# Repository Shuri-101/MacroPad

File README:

#Fracture Pad (A macro pad project) 
A macro Pad for use in CAD and general productivity + convenience, mainly for use in CAD... but up to you to decide what you want to use it for, I included an OLED screen to display things like animations or info like RAM usage...
# Orpheuspad

Orpheuspad is a 4 key macropad with a rotary encoder, an OLED Display. It also has 2 WS2812B Leds, and uses QMK firmware

It serves as an example piece/reference for the hackpad YSWS, since it contains an implementation of every common part.

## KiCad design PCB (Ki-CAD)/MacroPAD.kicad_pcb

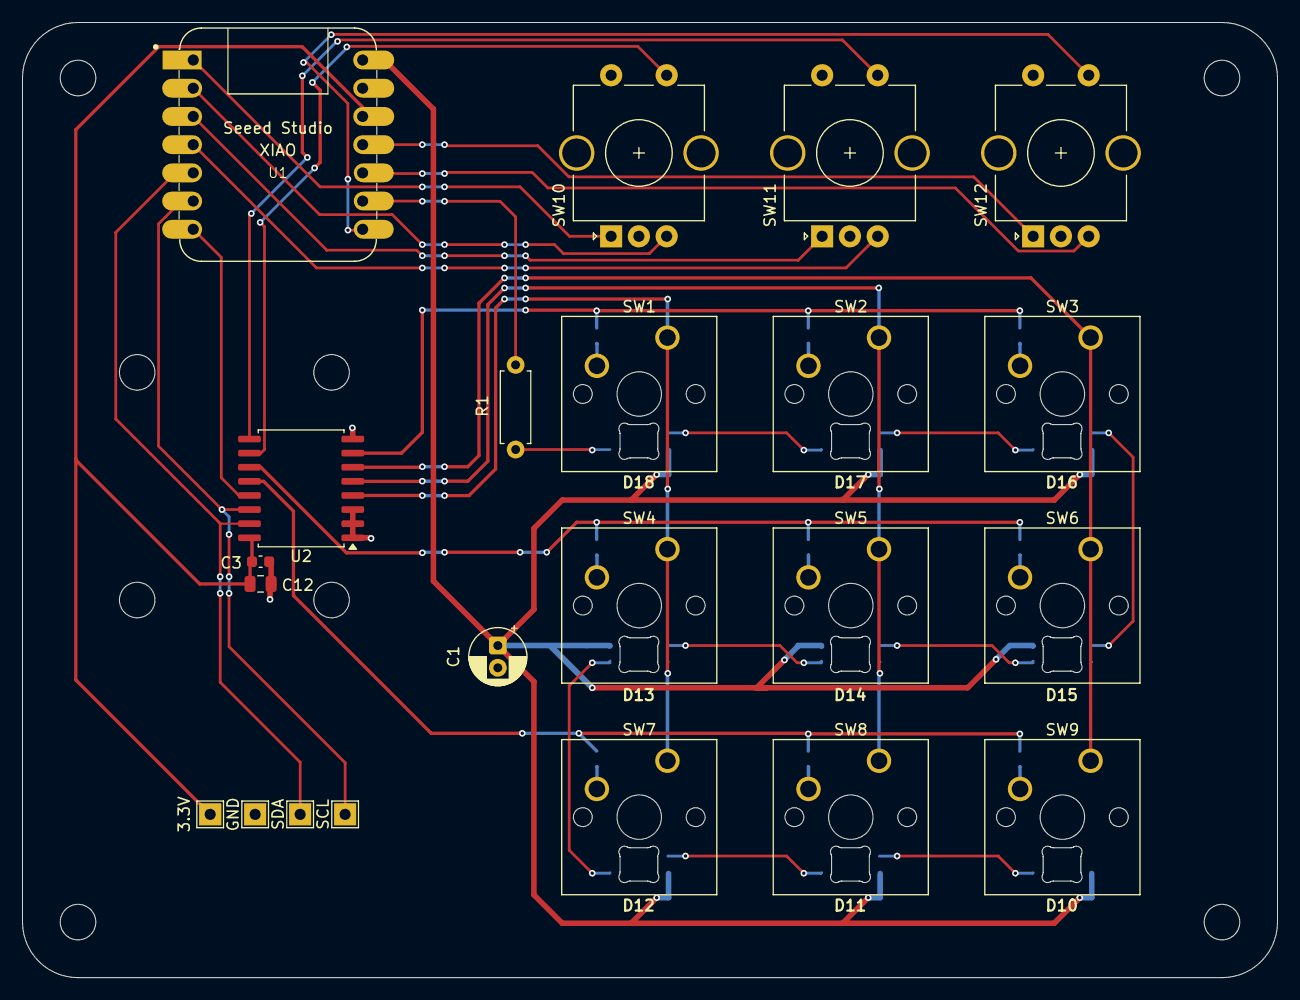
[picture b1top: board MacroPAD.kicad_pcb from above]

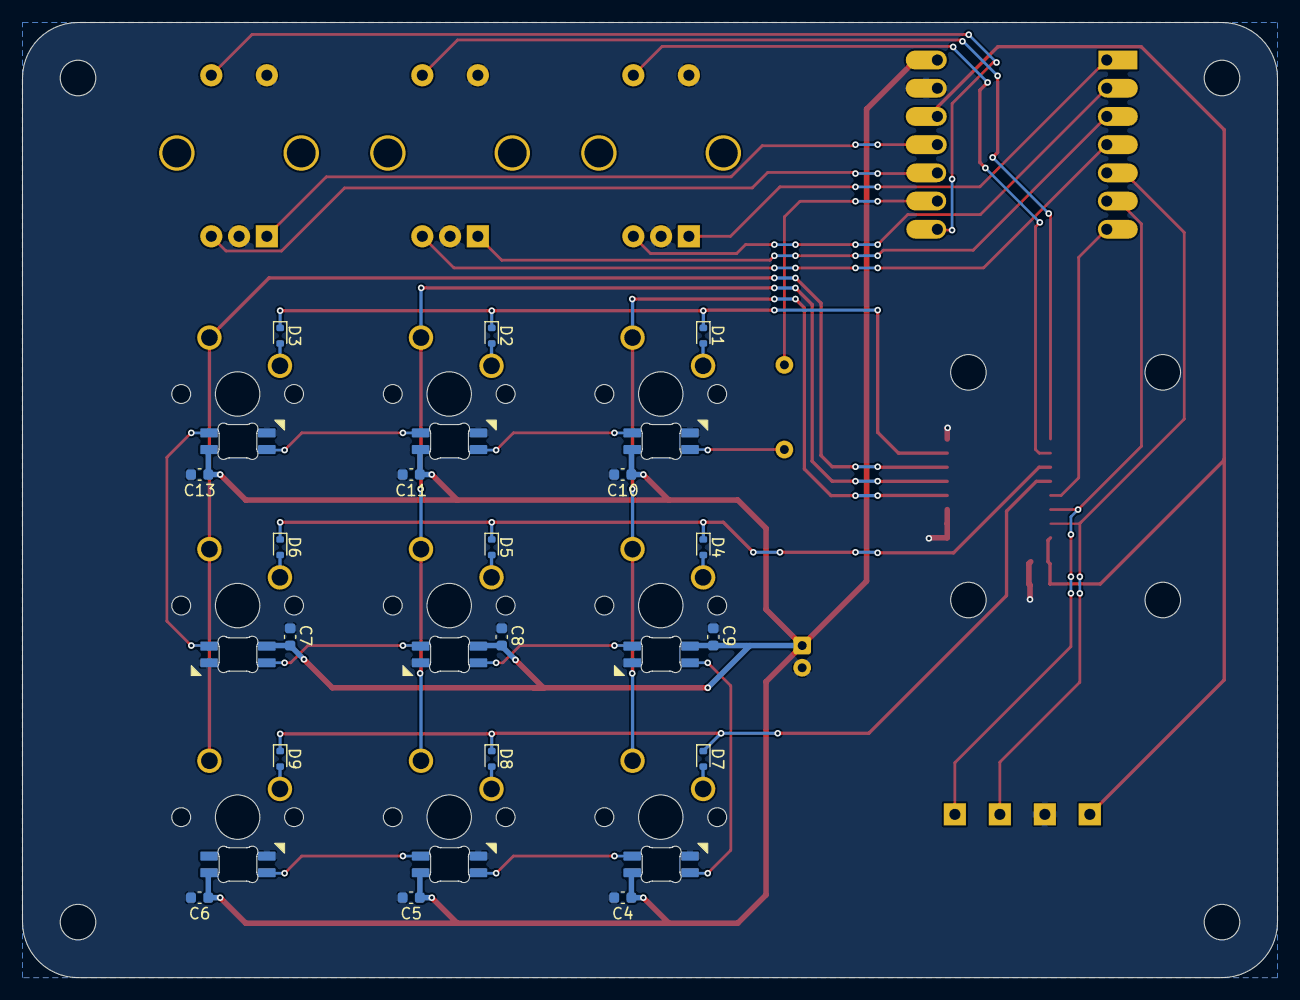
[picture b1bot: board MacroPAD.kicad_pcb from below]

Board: 2 copper layers, 113.0 x 86.0 mm, 49 parts (18 on the bottom side), 25 nets.

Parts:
3.3V: MountingHole_Pad; TestPoint_THTPad_2.0x2.0mm_Drill1.0mm
C1: 47uF; CP_Radial_D5.0mm_P2.00mm
C3, C4, C5, C6, C7, C8, C9, C10, C11, C13: 0.1uF; C_0603_1608Metric
C12: 4.7 µF; C_0805_2012Metric
D1, D2, D3, D4, D5, D6, D7, D8, D9: 1N4148WT; D_SOD-523
D10, D11, D12, D13, D14, D15, D16, D17, D18: SK6812MINI-E; SK6812MINI-E_fixed
GND: MountingHole_Pad; TestPoint_THTPad_2.0x2.0mm_Drill1.0mm
R1: 330R; R_Axial_DIN0207_L6.3mm_D2.5mm_P7.62mm_Horizontal
SCL: MountingHole_Pad; TestPoint_THTPad_2.0x2.0mm_Drill1.0mm
SDA: MountingHole_Pad; TestPoint_THTPad_2.0x2.0mm_Drill1.0mm
SW1, SW2, SW3, SW4, SW5, SW6, SW7, SW8, SW9: SW_Push; SW_Cherry_MX_1.00u_PCB
SW10, SW11: RotaryEncoder; RotaryEncoder_Alps_EC11E-Switch_Vertical_H20mm_CircularMoun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
SW12: RotaryEncoder_Switch; RotaryEncoder_Alps_EC11E-Switch_Vertical_H20mm_CircularMoun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
U1: MOUDLE-SEEEDUINO-XIAO; XIAO-Generic-Hybrid-14P-2.54-21X17.8MM
U2: PCF8574AT; SOIC-16W_7.5x10.3mm_P1.27mm

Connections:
3.3V: 3.3V.1, C3.1, C12.1, U1.12 (3V3), U2.16 (VDD)
5V: C1.1, C4.1, C5.1, C6.1, C7.1, C8.1, C9.1, C10.1, C11.1, C13.1, D10.1 (VDD), D11.1 (VDD), D12.1 (VDD), D13.1 (VDD), D14.1 (VDD), D15.1 (VDD), D16.1 (VDD), D17.1 (VDD), D18.1 (VDD), U1.14 (5V)
C1: SW1.1, SW4.1, SW7.1, U2.4 (P0)
C2: SW2.1, SW5.1, SW8.1, U2.5 (P1)
C3: SW3.1, SW6.1, SW9.1, U2.6 (P2)
GND: C1.2, C3.2, C4.2, C5.2, C6.2, C7.2, C8.2, C9.2, C10.2, C11.2, C12.2, C13.2, D10.3 (VSS), D11.3 (VSS), D12.3 (VSS), D13.3 (VSS), D14.3 (VSS), D15.3 (VSS), D16.3 (VSS), D17.3 (VSS), D18.3 (VSS), GND.1, SW10.C, SW10.S2, SW11.C, SW11.S2, SW12.C, SW12.S2, U1.13 (GND), U2.1 (A0), U2.2 (A1), U2.3 (A2), U2.8 (GND)
INT: U1.7 (PB08_A6_D6_TX), U2.13 (~INT)
Input A1: SW10.A, U1.1 (PA02_A0_D0)
Input A2: SW11.A, U1.3 (PA10_A2_D2)
Input A3: SW12.A, U1.11 (PA6_A10_D10_MOSI)
Input B1: SW10.B, U1.2 (PA4_A1_D1)
Input B2: SW11.B, U1.4 (PA11_A3_D3)
Input B3: SW12.B, U1.10 (PA5_A9_D9_MISO)
unnamed: D1.2 (A), D2.2 (A), D3.2 (A), D4.2 (A), D5.2 (A), D6.2 (A), D7.2 (A), D8.2 (A), D9.2 (A), SW1.2, SW2.2, SW3.2, SW4.2, SW5.2, SW6.2, SW7.2, SW8.2, SW9.2
unnamed: D18.4 (DIN), R1.2
unnamed: D10.2 (DOUT), D10.4 (DIN), D11.2 (DOUT), D11.4 (DIN), D12.2 (DOUT), D12.4 (DIN), D13.2 (DOUT), D13.4 (DIN), D14.2 (DOUT), D14.4 (DIN), D15.2 (DOUT), D15.4 (DIN), D16.2 (DOUT), D16.4 (DIN), D17.2 (DOUT), D17.4 (DIN), D18.2 (DOUT)
R1: D1.1 (K), D2.1 (K), D3.1 (K), U2.7 (P3)
R2: D4.1 (K), D5.1 (K), D6.1 (K), U2.11 (P6)
R3: D7.1 (K), D8.1 (K), D9.1 (K), U2.12 (P7)
RGB_DATA: R1.1, U1.9 (PA7_A8_D8_SCK)
S1A: SW10.S1A, U2.10 (P5)
S1B: SW11.S1B, U2.9 (P4)
S1C: SW12.S1C (S1), U1.8 (PB09_A7_D7_RX)
SCL: SCL.1, U1.6 (PA9_A5_D5_SCL), U2.14 (SCL)
SDA: SDA.1, U1.5 (PA8_A4_D4_SDA), U2.15 (SDA)
